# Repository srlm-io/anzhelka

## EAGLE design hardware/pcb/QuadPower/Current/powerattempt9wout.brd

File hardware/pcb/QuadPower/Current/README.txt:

Current:
Fixed ground plane.

To be completed:
Test REV A for other unseen problems.

REV A:
First version of the board to be approved to be milled.

Things to be fixed in:
Forget to put down a ground plane.
Forgot current limiting resistor on the DOUT pin of the MCP3208.

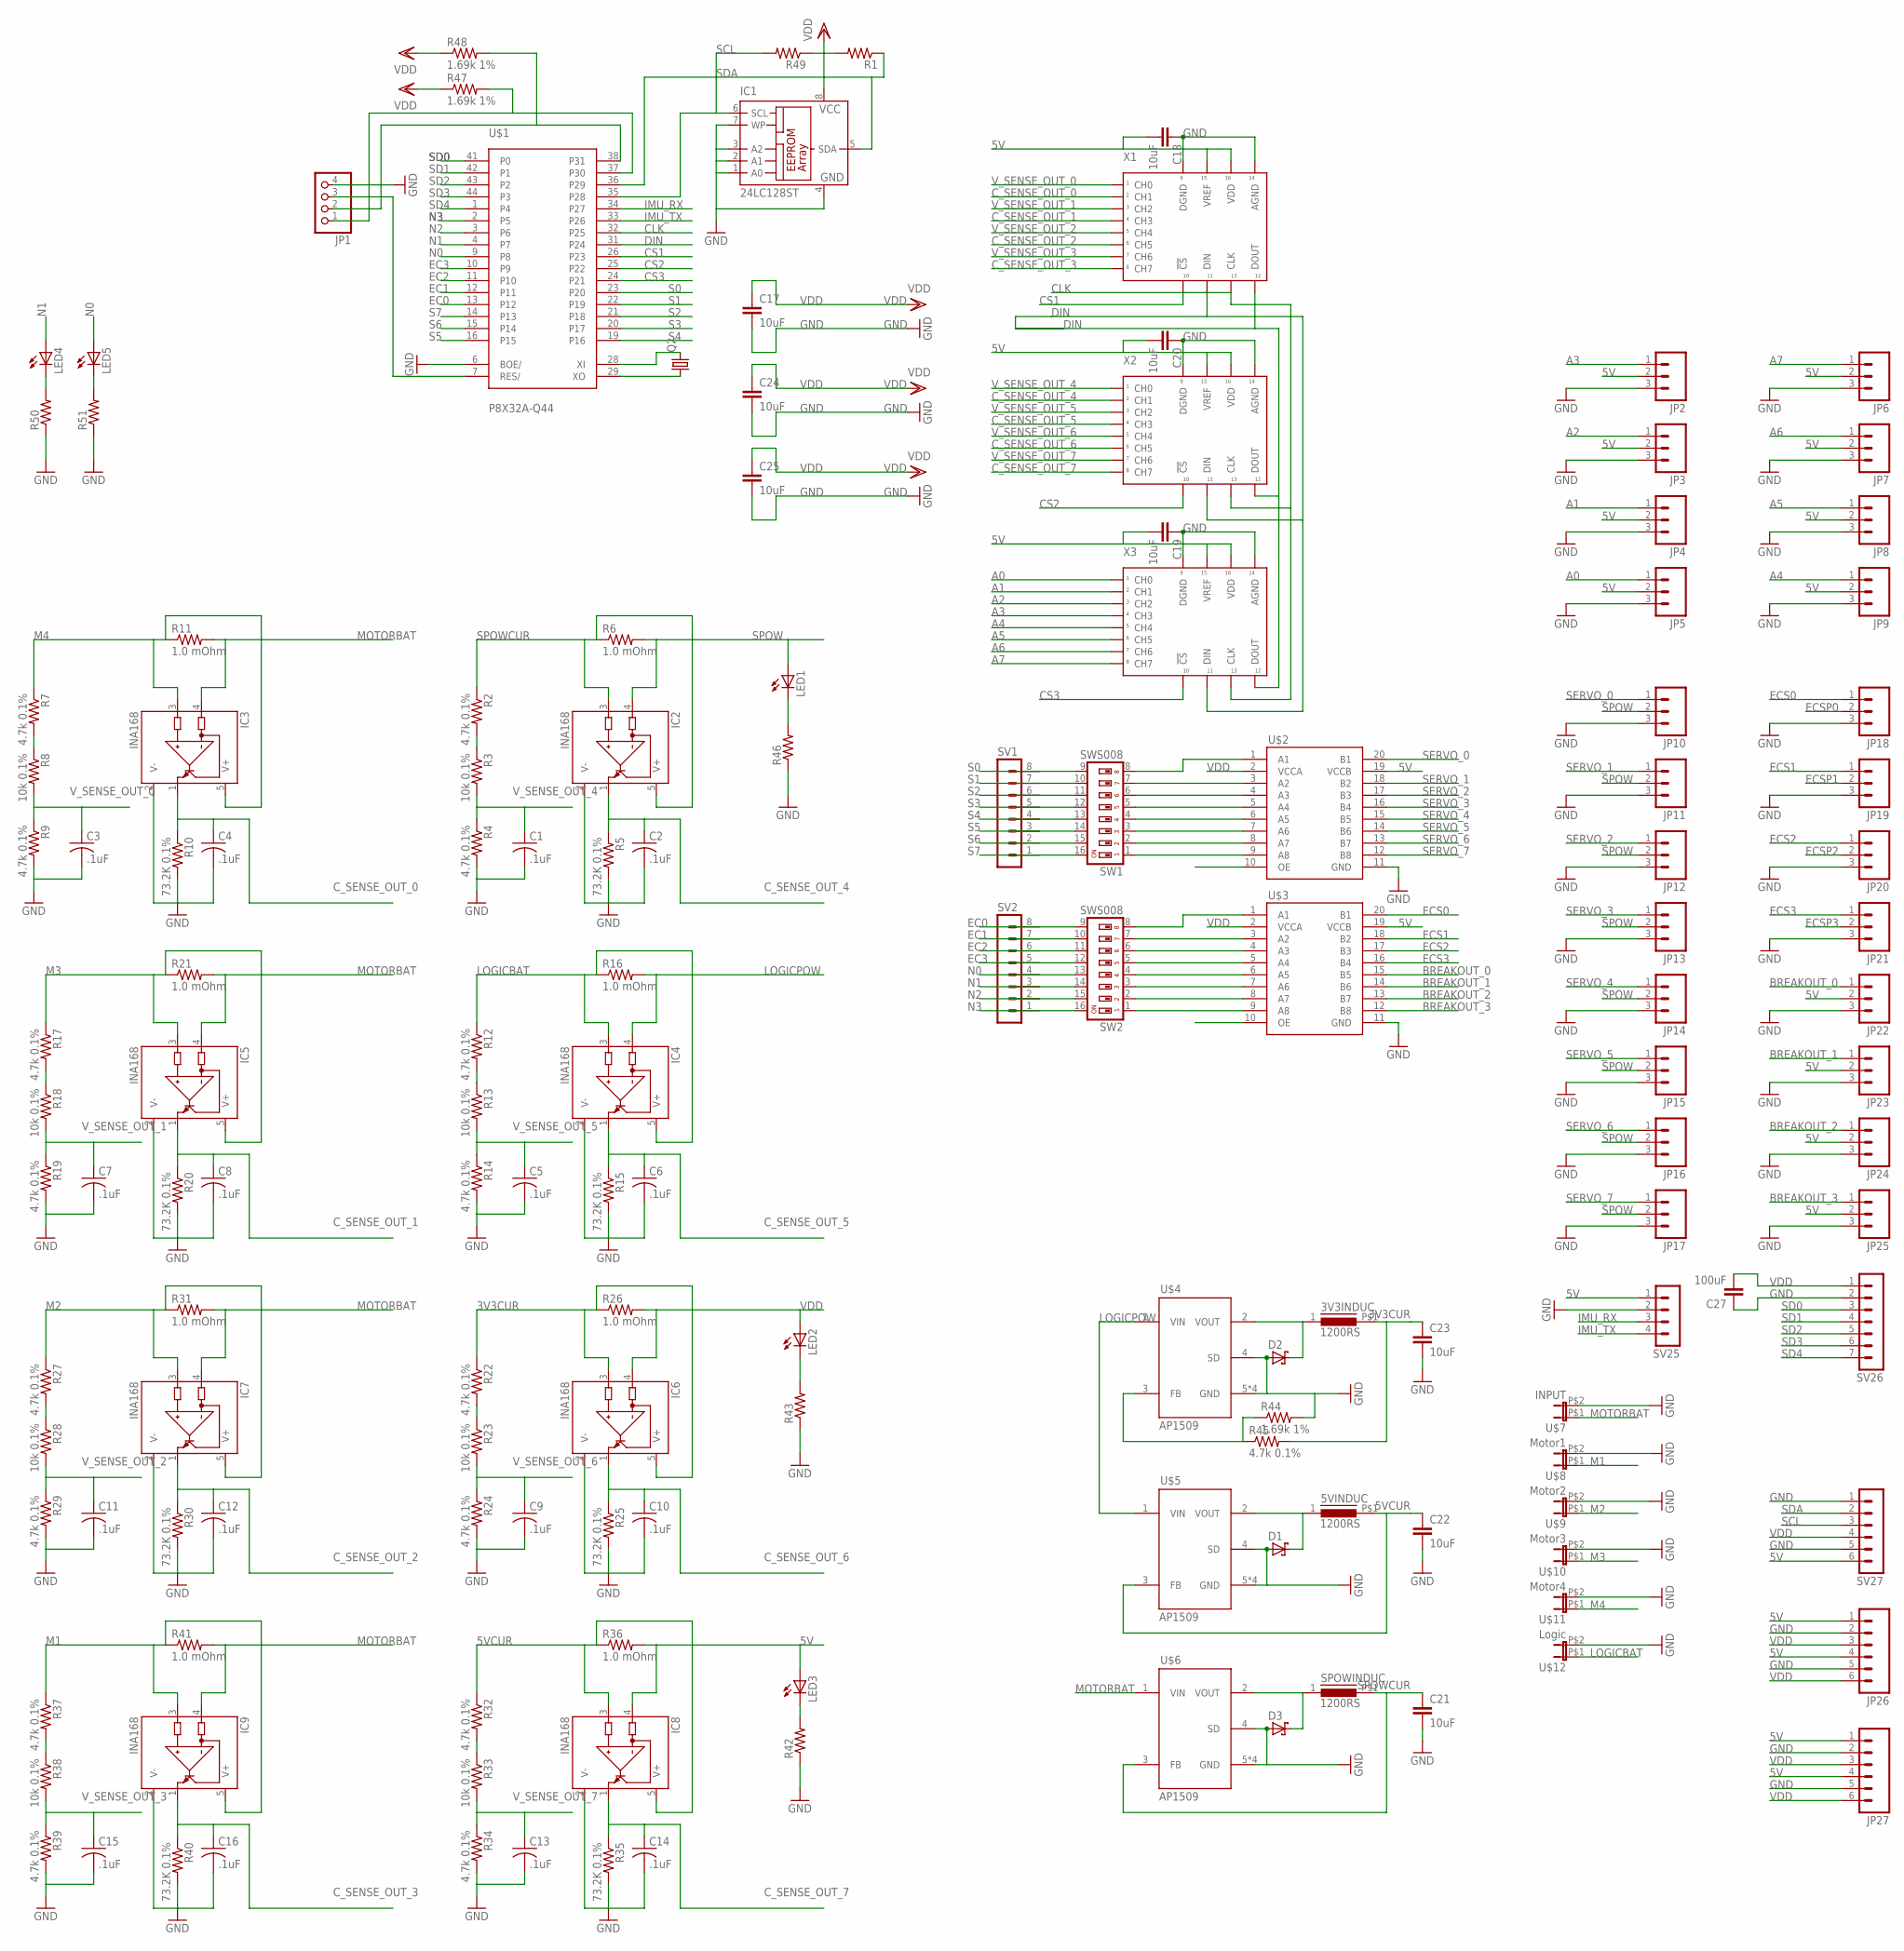
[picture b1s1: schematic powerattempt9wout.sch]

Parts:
3V3INDUC, 5VINDUC: 1200RS
C1, C2, C3, C4, C5, C6, C7, C8, C9, C10, C11, C12, C13, C14, C15, C16: .1uF; C0805
C17, C18, C19, C20, C21, C22, C23, C24, C25: 10uF; 1206
C27: 100uF; 1206
D1, D2, D3: SCHOTTKY-DIODESMD; SMB
IC1: 24LC128ST; TSSOP8
IC2, IC3, IC4, IC5, IC6, IC7, IC8, IC9: INA168; SOT23-5
JP1: PINHD-1X4/90; 1X04/90
JP2, JP3, JP4, JP5, JP6, JP7, JP8, JP9, JP10, JP11, JP12, JP13, JP14, JP15, JP16, JP17, JP18, JP19, JP20, JP21, JP22, JP23, JP24, JP25: M03PTH; 1X03
JP26, JP27: M06SIP; 1X06
LED1, LED2, LED3, LED4, LED5: LEDSML0805; SML0805
Q2: CRYSTALHC49S; HC49/S
R1, R49: R-US_M0805; M0805
R2, R4, R7, R9, R12, R14, R17, R19, R22, R24, R27, R29, R32, R34, R37, R39, R45: 4.7k 0.1%; 0805
R3, R8, R13, R18, R23, R28, R33, R38: 10k 0.1%; 0805
R5, R10, R15, R20, R25, R30, R35, R40: 73.2K 0.1%; 0805
R6, R11, R16, R21, R26, R31, R36, R41: 1.0 mOhm; LVK25
R42, R43, R46, R50, R51: RESISTOR0805-RES; 0805
R44, R47, R48: 1.69k 1%; 0805
SPOWINDUC: 1200RS
SV1, SV2: MA08-1
SV25: MA04-1
SV26: MA07-1
SV27: MA06-1
SW1, SW2: SWS008; SMS-008
U$1: P8X32A-Q44
U$2, U$3: TXB0108PWR; TSSOP20
U$4, U$5, U$6: AP1509; SO08
U$7: INPUT; DEANS
U$8: Motor1; DEANS
U$9: Motor2; DEANS
U$10: Motor3; DEANS
U$11: Motor4; DEANS
U$12: Logic; DEANS
X1, X2, X3: 21298ESMD; PDIP16

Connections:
3V3CUR: 3V3INDUC.P$1 (2), C23.1, IC6.3 (IN+), IC6.5 (V+), R22.1, R26.P$1 (1), R45.2
5V: C18.2, C19.2, C20.2, IC8.4 (IN-), JP2.2, JP3.2, JP4.2, JP5.2, JP6.2, JP7.2, JP8.2, JP9.2, JP22.2, JP23.2, JP24.2, JP25.2, JP26.1, JP26.4, JP27.1, JP27.4, LED3.A, R36.P$5 (2), SV25.1, SV27.6, U$2.19 (VCCB), U$3.19 (VCCB), X1.P$15 (VREF), X1.P$16 (VDD), X2.P$15 (VREF), X2.P$16 (VDD), X3.P$15 (VREF), X3.P$16 (VDD)
5VCUR: 5VINDUC.P$1 (2), C22.1, IC8.3 (IN+), IC8.5 (V+), R32.1, R36.P$1 (1), U$5.3 (FB)
A0: JP5.1, X3.P$1 (CH0)
A1: JP4.1, X3.P$2 (CH1)
A2: JP3.1, X3.P$3 (CH2)
A3: JP2.1, X3.P$4 (CH3)
A4: JP9.1, X3.P$5 (CH4)
A5: JP8.1, X3.P$6 (CH5)
A6: JP7.1, X3.P$7 (CH6)
A7: JP6.1, X3.P$8 (CH7)
BREAKOUT_0: JP22.1, U$3.15 (B5)
BREAKOUT_1: JP23.1, U$3.14 (B6)
BREAKOUT_2: JP24.1, U$3.13 (B7)
BREAKOUT_3: JP25.1, U$3.12 (B8)
CLK: U$1.32 (P25), X1.P$13 (CLK), X2.P$13 (CLK), X3.P$13 (CLK)
CS1: U$1.26 (P23), X1.P$10 (!CS)
CS2: U$1.25 (P22), X2.P$10 (!CS)
CS3: U$1.24 (P21), X3.P$10 (!CS)
C_SENSE_OUT_0: C4.1, IC3.1 (OUT), R10.1, X1.P$2 (CH1)
C_SENSE_OUT_1: C8.1, IC5.1 (OUT), R20.1, X1.P$4 (CH3)
C_SENSE_OUT_2: C12.1, IC7.1 (OUT), R30.1, X1.P$6 (CH5)
C_SENSE_OUT_3: C16.1, IC9.1 (OUT), R40.1, X1.P$8 (CH7)
C_SENSE_OUT_4: C2.1, IC2.1 (OUT), R5.1, X2.P$2 (CH1)
C_SENSE_OUT_5: C6.1, IC4.1 (OUT), R15.1, X2.P$4 (CH3)
C_SENSE_OUT_6: C10.1, IC6.1 (OUT), R25.1, X2.P$6 (CH5)
C_SENSE_OUT_7: C14.1, IC8.1 (OUT), R35.1, X2.P$8 (CH7)
DIN: U$1.31 (P24), X1.P$11 (DIN), X1.P$12 (DOUT), X2.P$11 (DIN), X2.P$12 (DOUT), X3.P$11 (DIN), X3.P$12 (DOUT)
EC0: SV2.8, SW2.9, U$1.13 (P12)
EC1: SV2.7, SW2.10, U$1.12 (P11)
EC2: SV2.6, SW2.11, U$1.11 (P10)
EC3: SV2.5, SW2.12, U$1.10 (P9)
ECS0: JP18.1, U$3.20 (B1)
ECS1: JP19.1, U$3.18 (B2)
ECS2: JP20.1, U$3.17 (B3)
ECS3: JP21.1, U$3.16 (B4)
ECSP0: JP18.2
ECSP1: JP19.2
ECSP2: JP20.2
ECSP3: JP21.2
GND: C1.2, C2.2, C3.2, C4.2, C5.2, C6.2, C7.2, C8.2, C9.2, C10.2, C11.2, C12.2, C13.2, C14.2, C15.2, C16.2, C17.2, C18.1, C19.1, C20.1, C21.2, C22.2, C23.2, C24.2, C25.2, C27.1, D1.A, D2.A, D3.A, IC1.1 (A0), IC1.2 (A1), IC1.3 (A2), IC1.4 (GND), IC1.7 (WP), IC2.2 (V-), IC3.2 (V-), IC4.2 (V-), IC5.2 (V-), IC6.2 (V-), IC7.2 (V-), IC8.2 (V-), IC9.2 (V-), JP1.4, JP2.3, JP3.3, JP4.3, JP5.3, JP6.3, JP7.3, JP8.3, JP9.3, JP10.3, JP11.3, JP12.3, JP13.3, JP14.3, JP15.3, JP16.3, JP17.3, JP18.3, JP19.3, JP20.3, JP21.3, JP22.3, JP23.3, JP24.3, JP25.3, JP26.2, JP26.5, JP27.2, JP27.5, R4.2, R5.2, R9.2, R10.2, R14.2, R15.2, R19.2, R20.2, R24.2, R25.2, R29.2, R30.2, R34.2, R35.2, R39.2, R40.2, R42.1, R43.1, R44.2, R46.1, R50.1, R51.1, SV25.2, SV26.2, SV27.1, SV27.5, U$1.5 (GND), U$1.6 (BOE/), U$1.17 (GND), U$1.27 (GND), U$1.39 (GND), U$2.11 (GND), U$3.11 (GND), U$4.4 (SD), U$4.5 (GND), U$4.6 (GND), U$4.7 (GND), U$4.8 (GND), U$5.4 (SD), U$5.5 (GND), U$5.6 (GND), U$5.7 (GND), U$5.8 (GND), U$6.4 (SD), U$6.5 (GND), U$6.6 (GND), U$6.7 (GND), U$6.8 (GND), U$7.P$2 (2), U$8.P$2 (2), U$9.P$2 (2), U$10.P$2 (2), U$11.P$2 (2), U$12.P$2 (2), X1.P$9 (DGND), X1.P$14 (AGND), X2.P$9 (DGND), X2.P$14 (AGND), X3.P$9 (DGND), X3.P$14 (AGND)
IMU_RX: SV25.3, U$1.34 (P27)
IMU_TX: SV25.4, U$1.33 (P26)
LOGICBAT: IC4.3 (IN+), IC4.5 (V+), R12.1, R16.P$1 (1), U$12.P$1 (1)
LOGICPOW: IC4.4 (IN-), R16.P$5 (2), U$4.1 (VIN), U$5.1 (VIN)
M1: IC9.3 (IN+), IC9.5 (V+), R37.1, R41.P$1 (1), U$8.P$1 (1)
M2: IC7.3 (IN+), IC7.5 (V+), R27.1, R31.P$1 (1), U$9.P$1 (1)
M3: IC5.3 (IN+), IC5.5 (V+), R17.1, R21.P$1 (1), U$10.P$1 (1)
M4: IC3.3 (IN+), IC3.5 (V+), R7.1, R11.P$1 (1), U$11.P$1 (1)
MOTORBAT: IC3.4 (IN-), IC5.4 (IN-), IC7.4 (IN-), IC9.4 (IN-), R11.P$5 (2), R21.P$5 (2), R31.P$5 (2), R41.P$5 (2), U$6.1 (VIN), U$7.P$1 (1)
N0: LED5.A, SV2.4, SW2.13, U$1.9 (P8)
N1: LED4.A, SV2.3, SW2.14, U$1.4 (P7)
N2: SV2.2, SW2.15, U$1.3 (P6)
N3: SV2.1, SW2.16, U$1.2 (P5)
unnamed: JP1.1, R47.2, U$1.37 (P30)
unnamed: JP1.2, R48.2, U$1.38 (P31)
unnamed: LED4.C, R50.2
unnamed: LED5.C, R51.2
unnamed: Q2.1, U$1.29 (XO)
unnamed: Q2.2, U$1.28 (XI)
unnamed: JP1.3, U$1.7 (RES/)
unnamed: R2.2, R3.1
unnamed: R7.2, R8.1
unnamed: R12.2, R13.1
unnamed: R17.2, R18.1
unnamed: R22.2, R23.1
unnamed: R27.2, R28.1
unnamed: R32.2, R33.1
unnamed: R37.2, R38.1
unnamed: SW1.8, U$2.1 (A1)
unnamed: SW1.7, U$2.3 (A2)
unnamed: SW1.6, U$2.4 (A3)
unnamed: SW1.5, U$2.5 (A4)
unnamed: SW1.4, U$2.6 (A5)
unnamed: SW1.3, U$2.7 (A6)
unnamed: SW1.2, U$2.8 (A7)
unnamed: SW1.1, U$2.9 (A8)
unnamed: SW2.8, U$3.1 (A1)
unnamed: SW2.7, U$3.3 (A2)
unnamed: SW2.6, U$3.4 (A3)
unnamed: SW2.5, U$3.5 (A4)
unnamed: SW2.4, U$3.6 (A5)
unnamed: SW2.3, U$3.7 (A6)
unnamed: SW2.2, U$3.8 (A7)
unnamed: SW2.1, U$3.9 (A8)
unnamed: LED1.C, R46.2
unnamed: LED2.C, R43.2
unnamed: LED3.C, R42.2
unnamed: 3V3INDUC.1, D2.C, U$4.2 (VOUT)
unnamed: 5VINDUC.1, D1.C, U$5.2 (VOUT)
unnamed: D3.C, SPOWINDUC.1, U$6.2 (VOUT)
unnamed: R44.1, R45.1, U$4.3 (FB)
S0: SV1.8, SW1.9, U$1.23 (P20)
S1: SV1.7, SW1.10, U$1.22 (P19)
S2: SV1.6, SW1.11, U$1.21 (P18)
S3: SV1.5, SW1.12, U$1.20 (P17)
S4: SV1.4, SW1.13, U$1.19 (P16)
S5: SV1.3, SW1.14, U$1.16 (P15)
S6: SV1.2, SW1.15, U$1.15 (P14)
S7: SV1.1, SW1.16, U$1.14 (P13)
SCL: IC1.6 (SCL), R49.2, SV27.3, U$1.35 (P28)
SD0: SV26.3, U$1.41 (P0)
SD1: SV26.4, U$1.42 (P1)
SD2: SV26.5, U$1.43 (P2)
SD3: SV26.6, U$1.44 (P3)
SD4: SV26.7, U$1.1 (P4)
SDA: IC1.5 (SDA), R1.1, SV27.2, U$1.36 (P29)
SERVO_0: JP10.1, U$2.20 (B1)
SERVO_1: JP11.1, U$2.18 (B2)
SERVO_2: JP12.1, U$2.17 (B3)
SERVO_3: JP13.1, U$2.16 (B4)
SERVO_4: JP14.1, U$2.15 (B5)
SERVO_5: JP15.1, U$2.14 (B6)
SERVO_6: JP16.1, U$2.13 (B7)
SERVO_7: JP17.1, U$2.12 (B8)
SPOW: IC2.4 (IN-), JP10.2, JP11.2, JP12.2, JP13.2, JP14.2, JP15.2, JP16.2, JP17.2, LED1.A, R6.P$5 (2)
SPOWCUR: C21.1, IC2.3 (IN+), IC2.5 (V+), R2.1, R6.P$1 (1), SPOWINDUC.P$1 (2), U$6.3 (FB)
VDD: C17.1, C24.1, C25.1, C27.2, IC1.8 (VCC), IC6.4 (IN-), JP26.3, JP26.6, JP27.3, JP27.6, LED2.A, R1.2, R26.P$5 (2), R47.1, R48.1, R49.1, SV26.1, SV27.4, U$1.8 (VDD), U$1.18 (VDD), U$1.30 (VDD), U$1.40 (VDD), U$2.2 (VCCA), U$3.2 (VCCA)
V_SENSE_OUT_0: C3.1, R8.2, R9.1, X1.P$1 (CH0)
V_SENSE_OUT_1: C7.1, R18.2, R19.1, X1.P$3 (CH2)
V_SENSE_OUT_2: C11.1, R28.2, R29.1, X1.P$5 (CH4)
V_SENSE_OUT_3: C15.1, R38.2, R39.1, X1.P$7 (CH6)
V_SENSE_OUT_4: C1.1, R3.2, R4.1, X2.P$1 (CH0)
V_SENSE_OUT_5: C5.1, R13.2, R14.1, X2.P$3 (CH2)
V_SENSE_OUT_6: C9.1, R23.2, R24.1, X2.P$5 (CH4)
V_SENSE_OUT_7: C13.1, R33.2, R34.1, X2.P$7 (CH6)

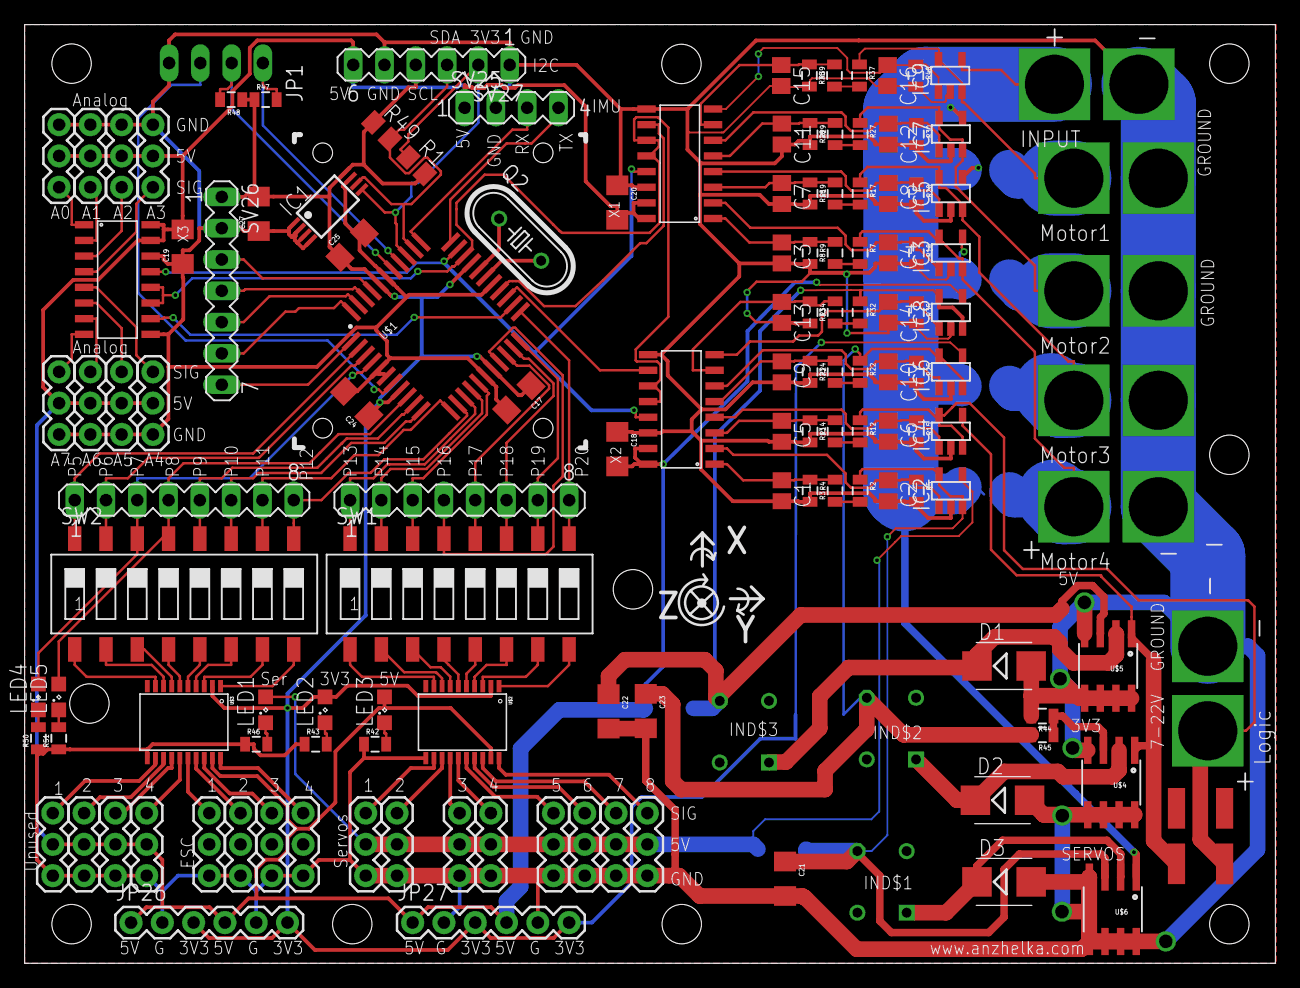
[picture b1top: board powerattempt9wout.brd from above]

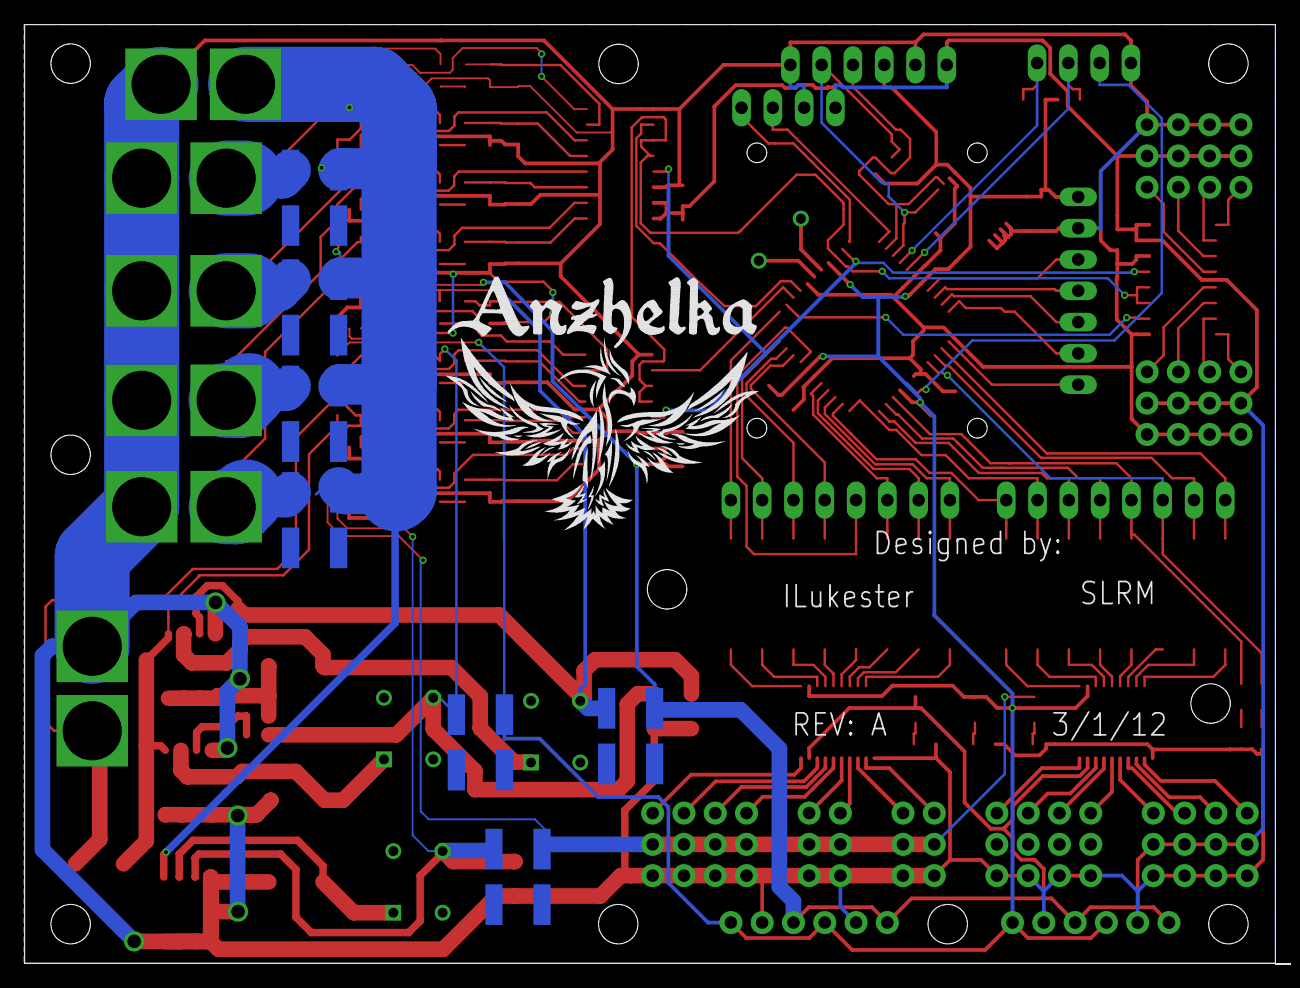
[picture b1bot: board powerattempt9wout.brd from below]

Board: 2 copper layers, 101.5 x 76.2 mm, 147 parts (7 on the bottom side), 122 nets.

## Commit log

2012-01-25 added label to FullDuplexSerialPlus (but this is really testing the branch feature...)
2012-01-31 File cleanup
2012-01-31 Almost all parts on single layer, currently will auto route without problems
    Reorganized pcbs files into directory.
2012-01-31 Setup basic directory structure, added support files (datasheets, compiler, etc.).
2012-01-31 Added some of Luke's datasheets
2012-02-02 Added a compile/download/terminal script for MPU6050
2012-02-13 Started work on the Python desktop terminal client
    Added the first CHR UM6 code, created a template script for compiling
    Updated the CHR_UM6 imu code, and added a generic spin template
2012-03-09 Started work on the Python desktop terminal client
    Added the first CHR UM6 code, created a template script for compiling
    Updated the CHR_UM6 imu code, and added a generic spin template
    updated something (but I don't remember what)
2012-03-09 Added some documentation, first revision of mathematics report, etc.
2012-03-10 Added REV-A and the current QuadPower Boards, removed old files
2012-03-15 Created introduction presentation, added system model diagram
2012-03-16 Updated presentation
2012-03-24 Started work on test stand.
2012-03-26 Began work on Test Stand code, added motor test results, added brushless rpm sensors
2012-04-05 Completed preliminary math analysis, worked some on IMU code.
2012-04-12 Updated Python Terminal GUI, created expo trifold text, updated serial driver. The Python terminal GUI can now has a working motors tab. This tab can be used to display the relevant aspects of each m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
2012-04-18 Added some netbook compatibility for the terminal programs
2012-04-18 Updated presentation slides with assorted information
2012-04-18 Quadrotor mathematics doc updated.
2012-04-19 Added automatic port detection for bst scripts, worked on test stand spin code.
2012-04-23 Added Alpha copy of quadrotor_report.
2012-04-23 Updated quadrotor report with some software specific line item. Cleaned up the directory as well (latex compilation files shouldn't be repo'd)
2012-04-23 Some spelling changes and a Test of Merging with Git
2012-04-23 more update work on the report.
2012-04-23 Fixed writing style and added some content
2012-04-23 Up to about 22 pages on the Report, several more things are needed.
2012-04-23 Cleaned up the report files, added some figures. Still needs more work.
2012-04-23 Cleaned up the quadrotor report. Organized and listed sections that still need to be completed.
2012-04-23 Cleaned up some of the display, added super COOL logo to bottom of page.
2012-04-23 Added sections to the two reports, made some clean ups.
2012-04-24 Version .04 fixed some gramtical errors, added weights,cleaned up report
2012-04-24 First complete working example of test stand code.
2012-05-01 Cleaned up repository structure, added specifications document outline
2012-05-01 Made the spin compiler script generic. Now use the compile.sh file, instead of bst_*.sh files.
2012-05-01 Created a directory cleanup script to get rid of annoying temporary files. Created single spin compiler script that takes a filename as it's argument.
2012-05-01 Developed workflow for assembly debugging, namely bstc *.list file assembly output list display.
2012-05-03 Updated compile script to have listgrep, updated listgrep to work correctly for the first object in the list file. Added interesting rampings to the test_stand.
2012-05-03 Worked a bit on the specifications document. Also added pyc files to clean.sh
2012-05-04 Added to sharon.anzh... There is still more needed, check the todo.
2012-05-04 Finished Section 2.3.2 in sharon.anz...
2012-05-05 Added user to specifications, did proofreading.
2012-05-05 Forgot to add oldgradstudent picture...
2012-05-09 Started section 4 (System Features)
2012-05-11 Foundations of UM6 work, tweeked listgrep and compile scripts
2012-05-14 First initial working version of UM6 interface object. Still needs work, but will accurately filter the incomming strings. Anything that can't be filtered gets put into a buffer for reading via stand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
2012-05-17 Created the motor block, updated the compile script, fixed a few bugs in the spin.lang syntax highlighting.
2012-05-21 Started work on moment block, initial work on parallelizing F32.
2012-05-24 Created the math compiler, implemented floating point routines and tests, completed initial work on motor and moment blocks
2012-05-25 Updated the Sharon Specs and some code in the Anzhelka terminal
2012-05-26 Updated sharon specification to include business requirements, functional reqirements, and feature description.
2012-05-27 worked on PID loop. Note: this build is incomplete, fails testing.
2012-05-28 Finished PID control loop F32_CMD block. 12 longs free.
2012-05-30 Updated serial port options. There may still be some programs that use the 4port object. Those need to switch to FastFDSBuffer. Created an anzhelka terminal test program to send 'random' strings. Did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
2012-05-31 Worked on the interface software. For this version, the main_output.spin program will take in commands for MKP, MKI, and MKD. It then processes the input, and echos to the terminal the respective val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
    '
2012-06-01 Seperated functionality into it's own files, updated compile script to support this seperation. Need to use one of two flags: --functions includes the anzhelka functions and variables --mathfunctions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
2012-06-02 I have updated the terminal so that it now accepts 2 way Serial. To send a command just type into the main display box in Motors -> Vars. Press Update to send the command. Besure to enter your correc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
2012-06-02 fixed bug where if no data is received it's a constant stream of errors. See diff
2012-06-02 Test stand PID now works, suitable for testing with the terminal program. Need to find the PID constants.
2012-06-03 Add true selection functionality to the Anzhelka Termainal under the Motors -> Vars tab
2012-06-03 Worked on making the terminal bug free.
2012-06-04 Fixed whacky order on Linux for dropdown boxes, Now has graph options for X length and var to be graphed, pressing enter in a value box sends the update string for said box, update all button work
2012-06-04 Worked on integrating the systems. And breaking Luke's console.
2012-06-04 Fixed problems with terminal
2012-06-05 Multiple graph items, stop all functionality added.
2012-06-05 Fixed 1 being sent on connect. I believe that PWM now properly sends. Newline char is now sent after transimission. NID is now sending the proper var.
2012-06-05 Fixed Min sliderbox bug. Separate lookup table for selecting the Variable to change. StopAll is tested and working on linux and windows. You can now set default items to be graphed or loaded into var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
2012-06-06 Anzhelka terminal now has: A title, Editable Upper and Lower bounds, Box2Slider now button is now named Defaults and resets the slider to the default position, there is now a default position placeme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
2012-06-07 Lots of work, in several areas.
2012-06-07 Added new variables. When you click on the Motors->Angles tab the graphing options change to angle graph options, when you click back on another tab it will show the original graphing options. Added 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
2012-06-08 Final attempt, not working...
2012-06-09 Updated slides for final presentation.
2012-06-12 Fixed typos in ENGR180W report.
2012-06-12 Made changes to the quadrotor report for EE175
2012-06-12 Updated the ATXXX table in the report, changed some section titles.
2012-06-16 Updated sections 3.10, 3.11, and added Luke's part to 3.8 of the final report.
2012-06-16 Fixed section 2.6 and added information to 3.4
2015-03-14 Migrating wiki contents from Google Code

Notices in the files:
parts and their libraries:
SparkFun: Licensing: CC v3.0 Share-Alike You are welcome to use this library for commercial purposes.
